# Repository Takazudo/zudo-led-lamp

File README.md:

# zudo-led-lamp

USB-PD powered LED lamp with fire/wave-like brightness modulation.

Docs: https://zudo-led-lamp.takazudomodular.com/

## Current build path

The current path is zudo-pd **P15 r1** (27 × 40 mm, 3 A NVM image) with the two existing
Board Ls, decided 2026-11-03. The two Board Ls already exist; the P15 modules are not ordered, programmed or measured. See the
[current path](candidates/README.md#current-path-p15-r1--the-two-existing-board-ls) for the
exact revisions and hashes, and the
[before-programming checklist](firmware/board-l/BEFORE-PROGRAMMING-CHECKLIST.md) before any
power-on. `boards/board-p/` remains the as-ordered 2026-09-19 Board P reference.
The [current state and completion page](doc/src/content/docs/architecture/current-state.mdx)
lists what is ordered, programmed and measured, and the owner actions in order.

Start the two-P15 order preparation at the [prototype-order handoff](manufacturing/README.md).
Supplier preview, order-day availability and total cost remain owner checkout gates.

## Repo layout

- `doc/` — zudo-doc documentation site (source of truth for specs, notes, and build logs)
- `boards/board-p/` — KiCad project: USB-PD front end board
- `boards/board-l/` — KiCad project: driver + control + LED array board
- `boards/swd-adapter/` — KiCad project: ST-LINK/V2 20-pin to Board L 1x5 SWD adapter
- `enclosure/` — parametric starburst enclosure generator and [print/assembly guide](enclosure/README.md)
- `symbols/`, `footprints/` — shared KiCad symbol/footprint/3D libraries for all projects (see `footprints/CLAUDE.md`)

## Component selection

Read the [draft selection and socket comparison guidance](doc/src/content/docs/architecture/component-selection-guidelines.mdx) before proposing parts. Exact evidence ownership remains in the component-spec-audit inventory.

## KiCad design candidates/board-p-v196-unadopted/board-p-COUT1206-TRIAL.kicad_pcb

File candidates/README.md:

# Isolated hardware candidates — NOT ADOPTED

Directories here hold isolated design candidates imported from outside Git history
for review. They are not canonical hardware: `boards/` and
`manufacturing/` remain the source of truth for what was ordered. Nothing here is
validated, qualified, released, or order-ready, and no fabrication output may be
generated from it without a separate explicit approval.

## Current path: P15 r1 + the two existing Board Ls

**Decision 2026-11-03 (owner):** the LED lamp's current Board P is the zudo-pd
**P15 r1**, shared with the 15 V zudo-pd product, mated with the **two existing Board Ls**
from the 2026-09-19 order. LED-first. The Board Ls already exist; P15 is not ordered, programmed or
measured yet.

| Item | Current value | Where it lives |
| --- | --- | --- |
| Board P | zudo-pd `boards/board-p15/` r1, 27 × 40 mm, same outline, holes and JOUT1 as the ordered LED Board P | Adopted at zudo-pd commit `4a0741fabf8d2332848a3740708aab26b8504133` (now on zudo-pd `main`). Consumer reference: [`boards/p15-r1-reference.json`](../boards/p15-r1-reference.json), checked by `python3 scripts/checks/verify-p15-reference.py --pd-repo <zudo-pd checkout>` (byte identity only) |
| NVM image | `boards/board-p15/nvm/stusb4500-15v.bin`: 2 PDOs, PDO1 5 V / 1.5 A, PDO2 15 V / **3 A**, POWER_ONLY_ABOVE_5V = 1. Same image for LED and zudo-pd | SHA256 `76622e14862e53cf318b24eb662f7dc9f34d48134867cf954b30c195c26e8eeb` at that commit. Desk image: never written or read back |
| Board L | The two existing boards, unchanged: RS1 = 200 mΩ as built, MCU believed blank | `boards/board-l/`, `manufacturing/jlcpcb/2026-09-19/` |
| Firmware | `firmware/board-l/target/` with `CTRL_FULL_CCR` = 2407 (the 200 mΩ ceiling) | Not flashed. See [`firmware/board-l/BEFORE-PROGRAMMING-CHECKLIST.md`](../firmware/board-l/BEFORE-PROGRAMMING-CHECKLIST.md) |
| Bench sheets | Boot, NTC, knob, CTRL, option bytes, temperature | [`firmware/board-l/BENCH-TEST-SHEETS.md`](../firmware/board-l/BENCH-TEST-SHEETS.md), all NOT EXECUTED |

Accepted residuals and mandatory steps (they are not passes):

- P15 has no NVM-independent voltage window or eFuse. Requirement rows R2.3, R2.4 and
  R2.6 are **FAIL** and R2.5 is **UNKNOWN**; the owner accepted this as a prototype-stage
  residual. The adoption does not turn them into passes.
- Every P15 unit must have its NVM written and accepted (P15-NVM-4/5 on a 5 V-only source,
  then P15-NVM-6 on a PD test source with no load) before it ever mates with a Board L.
  The procedure is owned by zudo-pd (`doc/src/content/docs/architecture/board-p15-programming.md`).
- Keep `CTRL_FULL_CCR` = 2407 while RS1 = 200 mΩ. The [#52 analysis](board-l-led-margin-52/ANALYSIS.md)
  hot-branch numbers (88.6 / 96.9 mA at full CTRL) and the 250 mΩ rework numbers
  (72.5 / 79.1 mA) are sensitivity cases, not measured values or guaranteed limits. Do not
  rework RS1 or move to 3200 as an assumed next step.

Enclosure fit in CAD (2026-11-03, P15P): `enclosure/generate.py` at `cfc8cb4`, run in an isolated
copy with `boards/board-p/board-p.kicad_pcb` replaced by the zudo-pd P15 r1 PCB (sha256 `97acc5f4…`)
and its 3D models, KiCad 10.0.6 pinned image, exit 0. All generator assertions and `check_stack` pass,
every printed part clears every P15 and Board L STEP body (0.0 mm³), and the USB corridor is open.
Tracked enclosure outputs were not regenerated. Nominal datums only; print and seating fit are unmeasured.
Use the [LED prototype-order handoff](../manufacturing/README.md) for the pinned owner decision packet,
exact three upload files, supporting exclusions and remaining checkout checks. For LED, 2 P15 are new,
the 2 Board Ls are reused, and no new Board B is ordered.

These are **not** blockers for the current path: the PDO2 1.5 A vs 3 A question (settled:
3 A), the 27 × 44 / 27 × 50 outline question, and the old Board P #144 diagnosis. They
belong to the future candidates below.

## Future candidates (not on the current path)

| Directory | Candidate | State |
| --- | --- | --- |
| [`board-p-v196-unadopted/`](board-p-v196-unadopted/PROVENANCE.md) | HUSB238_006DD 15 V-only shared Board P, V196 routed PCB | FUTURE CANDIDATE. UNADOPTED; native DRC exit 5 (22 known findings), not DRC PASS |
| [`board-p-v198-unadopted/`](board-p-v198-unadopted/PROVENANCE.md) | V196 + PCB/schematic field sync, J1 bound to USB4105-GF-A / C3020560 | FUTURE CANDIDATE. UNADOPTED; same 22 DRC findings (exit 5), not DRC PASS |
| [`board-p-v199-pending-user-decision/`](board-p-v199-pending-user-decision/PROVENANCE.md) | V198 + recommended options as separable changes: RMH2 187k, COUT Datasheet sync, J1 GND 0.025 mm trim, SMAJ20A input TVS | FUTURE CANDIDATE (its options are no longer pending for the current path). UNADOPTED scratch; same 22 DRC findings with default rules (exit 5); 0 with the unapplied base rules in a scratch copy only |
| [`board-p-rnext-stusb-unadopted/`](board-p-rnext-stusb-unadopted/README.md) | LED Board P r-next schematic: zudo-pd common STUSB4500 block @3ac13d46 + LED voltage window after Q1 + JOUT1; option pair PDO2 1.5 A / RILM 3.32 k or 3 A / 1.27 k (candidate-only question) | **FUTURE CANDIDATE** (deferred 2026-11-03; its PDO2 and outline options are not current blockers). UNADOPTED schematic draft; native netlist matches spec, ERC 0 errors / 13 pin-type warnings; 9 candidate owner bundles; land check; 27 × 40 mm placement study (no routing); area options (C3 / J3 / back side / outline) compared, J3 test-pad array adopted in candidate; no PCB |
| [`board-p-stusb-window-subcircuit/`](board-p-stusb-window-subcircuit/README.md) | LED Board P r-next voltage window (TPS3701 + TPS25947 + QINH driven by STUSB4500 VBUS_EN_SNK, RMH2 187 k, SMAJ20A input TVS) as a standalone sub-circuit | FUTURE CANDIDATE. UNADOPTED desk source; structural check + V196 arithmetic only; awaits the common STUSB4500 block |
| [`board-p-stusb4500-144-root-cause/`](board-p-stusb4500-144-root-cause/ANALYSIS.md) | Issue #144 desk root-cause ranking for the ordered STUSB4500 Board P and rules for the common controller block | Desk analysis only; nothing measured or changed. Not a prerequisite for the current path |
| [`board-l-led-margin-52/`](board-l-led-margin-52/ANALYSIS.md) | Issue #52 LED peak-current desk analysis: RS1 options vs firmware CTRL ceiling | UNADOPTED proposal; recommends RS1 = 250 mΩ (RLP25FEER250, LCSC unverified); no hardware changed. The current path keeps 200 mΩ with `CTRL_FULL_CCR` 2407 |
| [`FIRMWARE-V72-INVENTORY.md`](FIRMWARE-V72-INVENTORY.md) | Board L V72 portable C firmware, imported to [`firmware/board-l/`](../firmware/board-l/README.md) | Imported; the target skeleton in `firmware/board-l/target/` links it. Not flashed |

The KiCad project directories sit two levels below the repository root on purpose:
their library footprints resolve 3D models via
`${KIPRJMOD}/../../footprints/kicad/zudo-led-lamp.3dshapes/`.

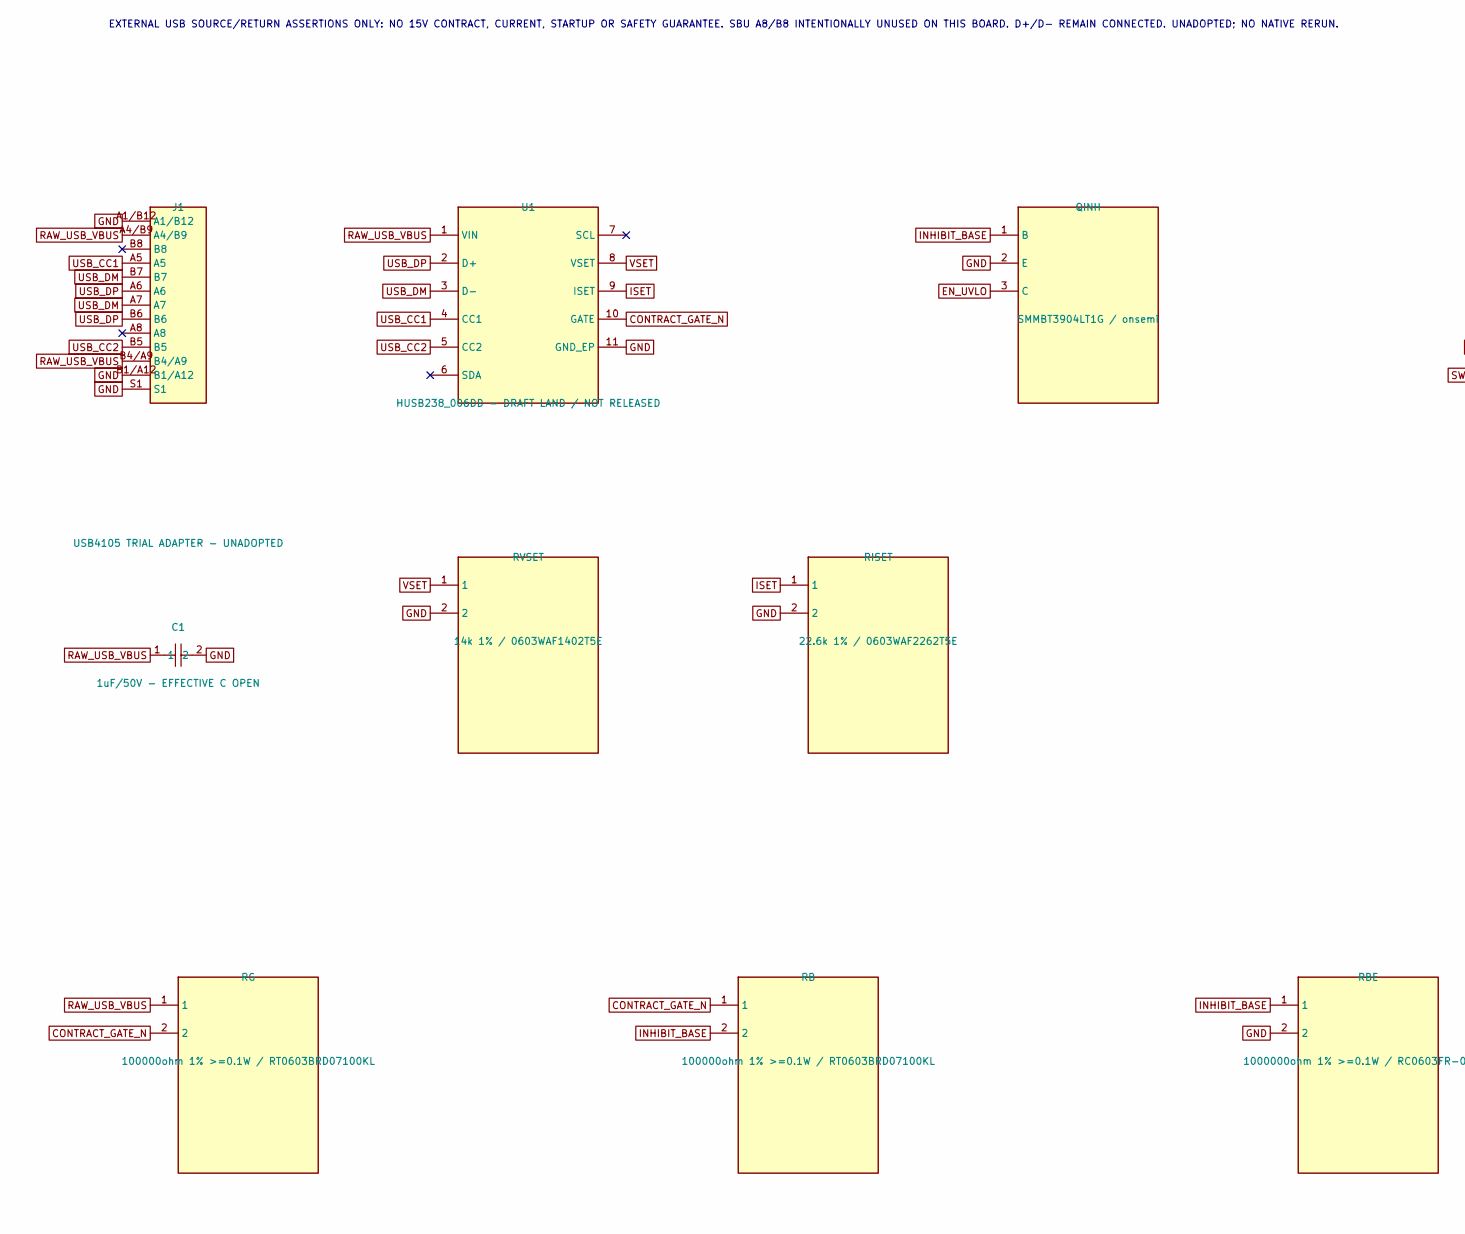
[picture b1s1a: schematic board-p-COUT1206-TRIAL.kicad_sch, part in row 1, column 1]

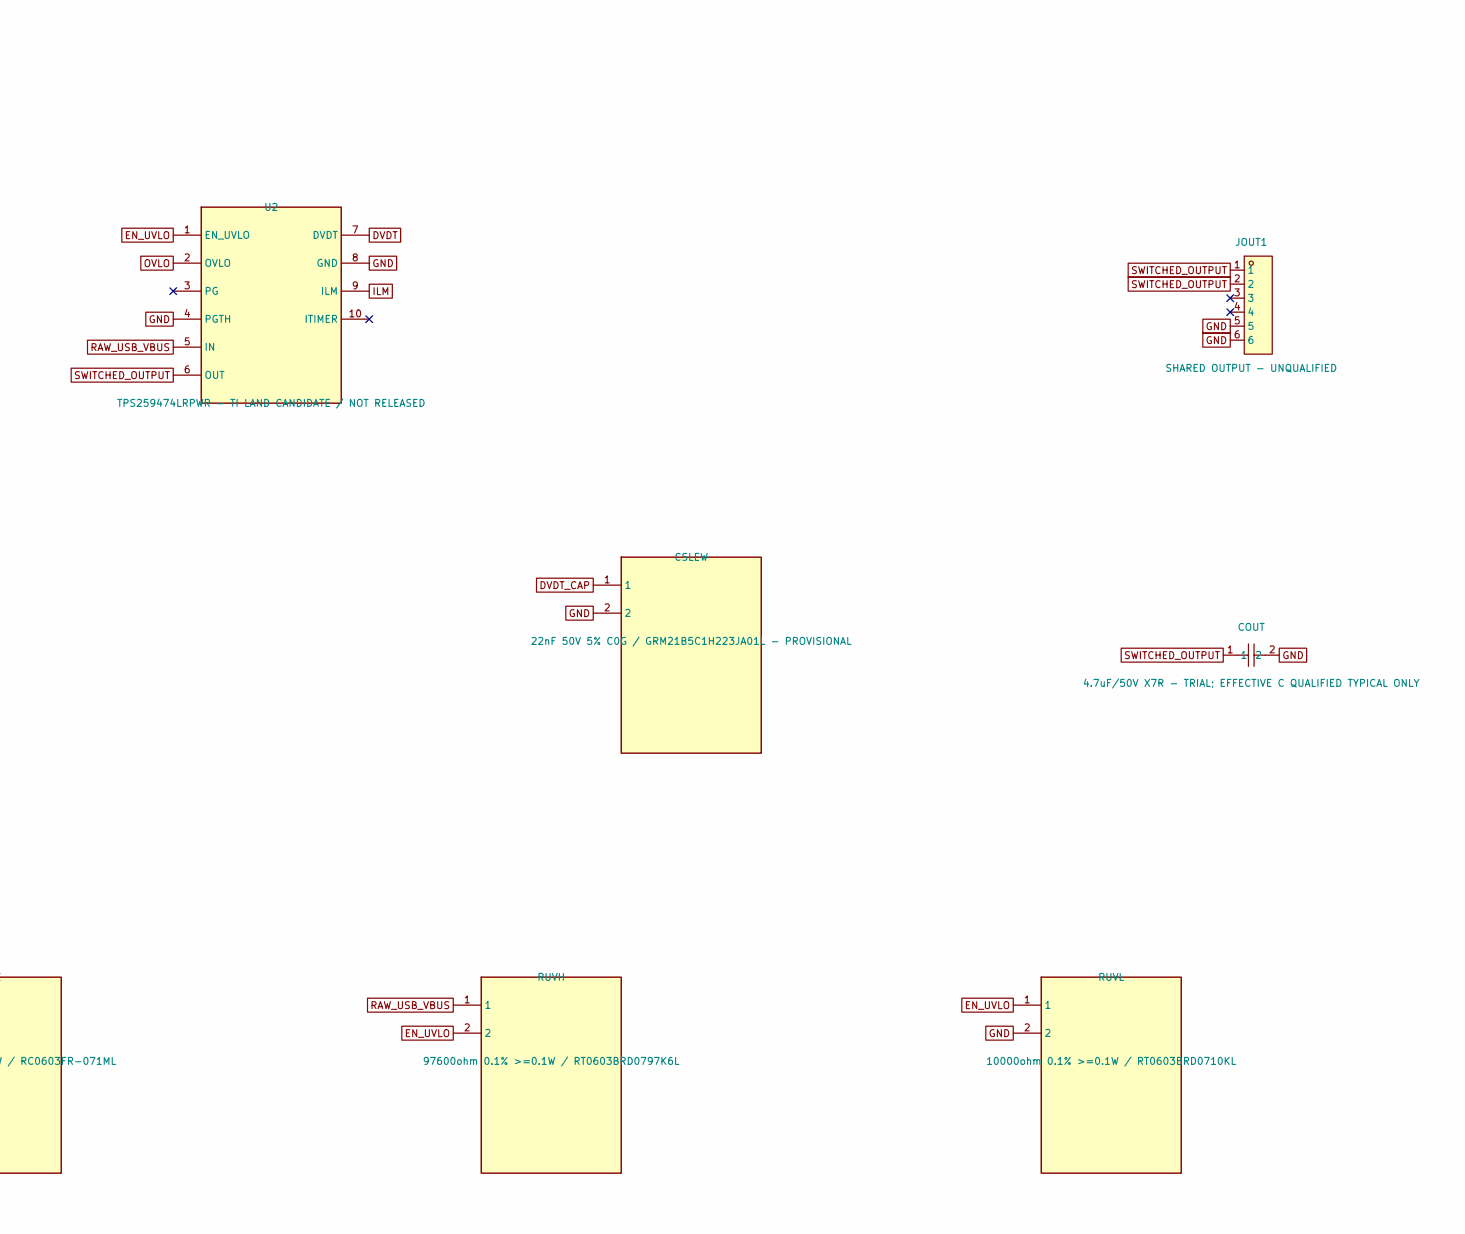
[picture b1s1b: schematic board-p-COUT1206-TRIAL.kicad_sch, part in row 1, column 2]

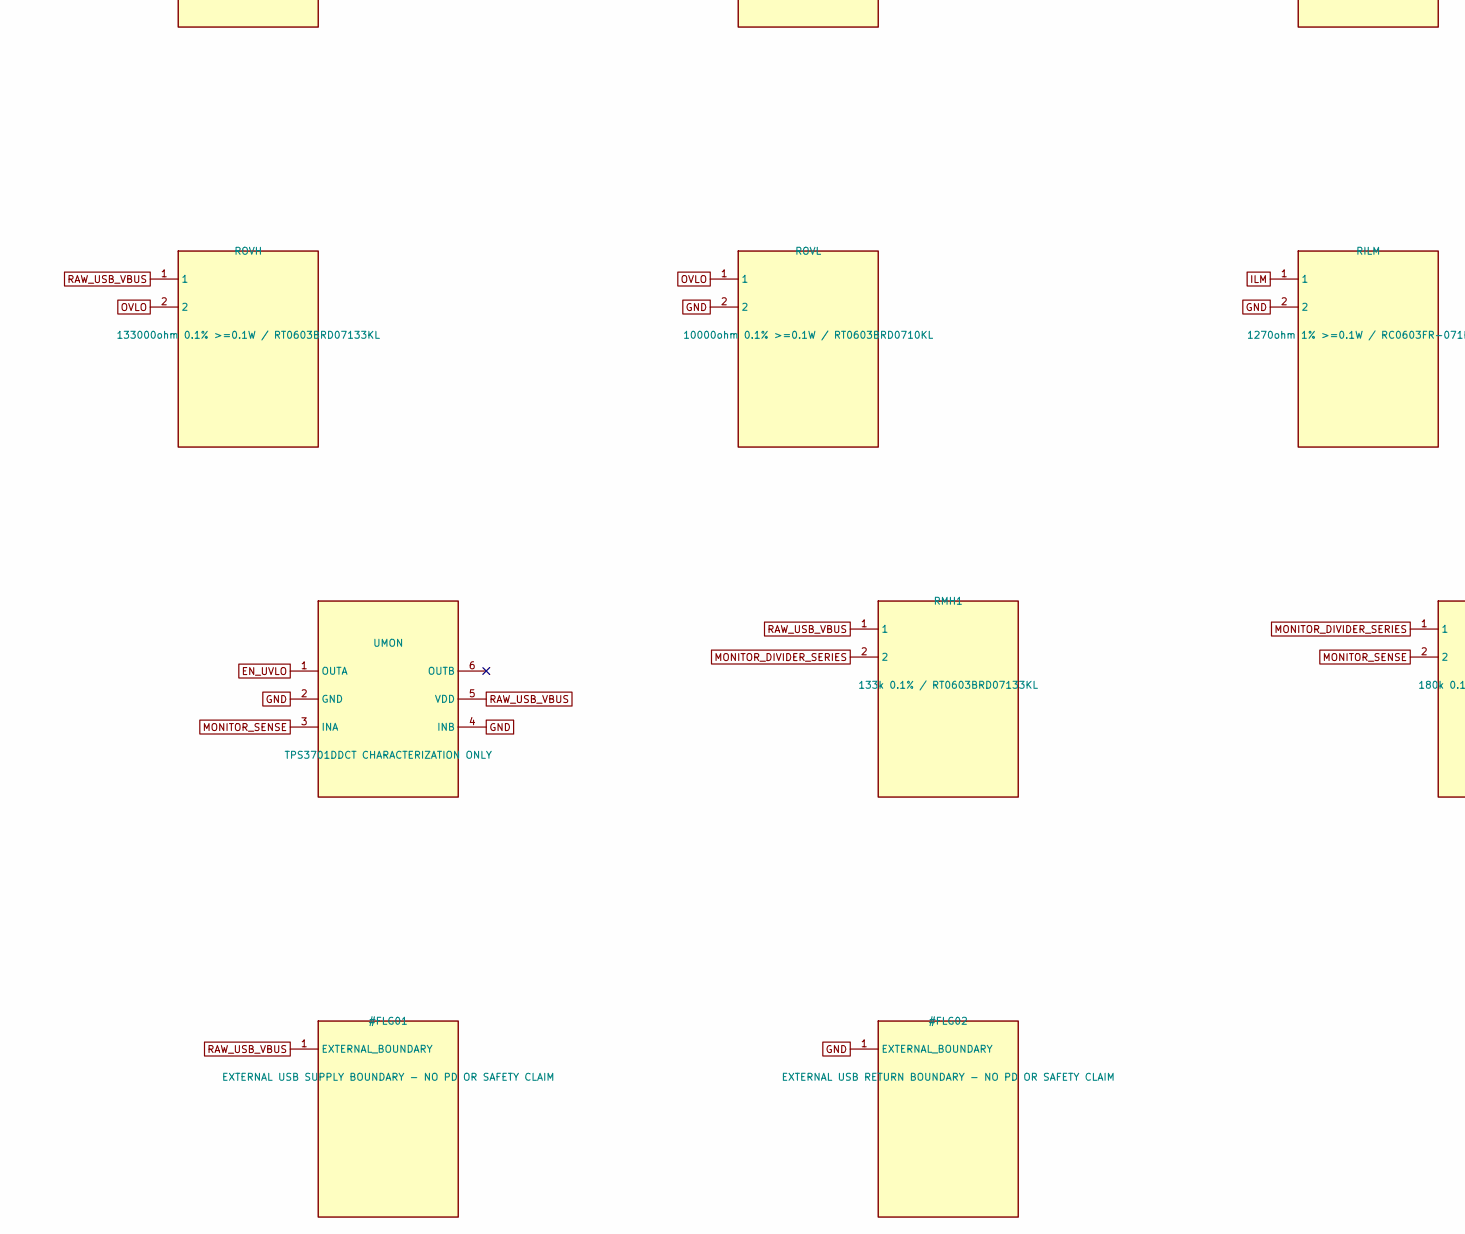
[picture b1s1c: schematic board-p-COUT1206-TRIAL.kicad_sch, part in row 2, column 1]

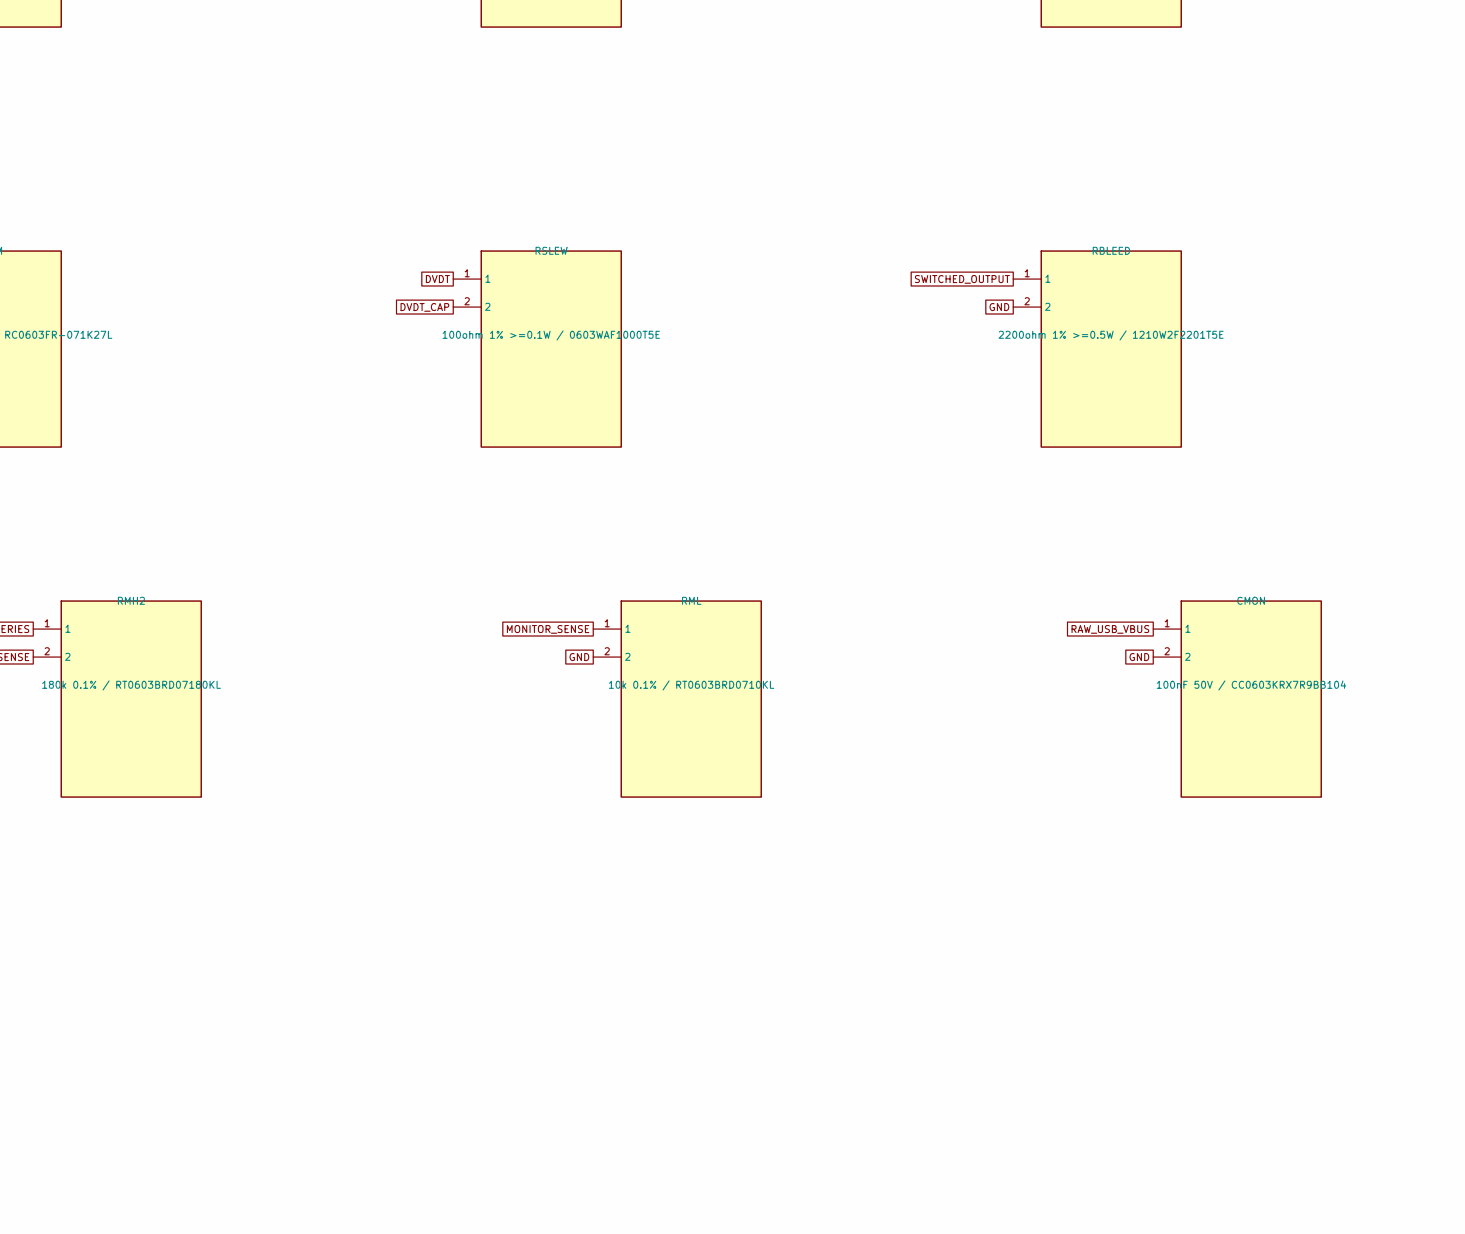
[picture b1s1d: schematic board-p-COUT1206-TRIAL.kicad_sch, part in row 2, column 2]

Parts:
C1: 1uF/50V - EFFECTIVE C OPEN; C0603; LCSC C15849
CMON: 100nF 50V / CC0603KRX7R9BB104; C0603; LCSC C14663
COUT: 4.7uF/50V X7R - TRIAL; EFFECTIVE C QUALIFIED TYPI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; COUT_CL31B475KBHNNNE_1206_TRIAL; MPN CL31B475KBHNNNE; LCSC C51205
CSLEW: 22nF 50V 5% C0G / GRM21B5C1H223JA01L - PROVISIONAL; GRM21B5C1H223JA01L_MURATA_REFLOW; LCSC C77069
J1: USB4105 TRIAL ADAPTER - UNADOPTED; USB4105_V106_TRIAL_UNASSIGNED
JOUT1: SHARED OUTPUT - UNQUALIFIED; HDR-TH_6P-P2.54-V-M; LCSC C492405
QINH: SMMBT3904LT1G / onsemi; SMMBT3904LT1G_CASE318_ONSEMI_EXAMPLE; LCSC C84555
RB: 100000ohm 1% >=0.1W / RT0603BRD07100KL; R0603; LCSC C122538
RBE: 1000000ohm 1% >=0.1W / RC0603FR-071ML; R0603; LCSC C105578
RBLEED: 2200ohm 1% >=0.5W / 1210W2F2201T5E; RBLEED_1210W2F2201T5E; LCSC C422361
RG: 100000ohm 1% >=0.1W / RT0603BRD07100KL; R0603; LCSC C122538
RILM: 1270ohm 1% >=0.1W / RC0603FR-071K27L; R0603; LCSC C245930
RISET: 22.6k 1% / 0603WAF2262T5E; R0603; LCSC C22959
RMH1: 133k 0.1% / RT0603BRD07133KL; R0603; LCSC C861111
RMH2: 180k 0.1% / RT0603BRD07180KL; RMH2_RT0603BRD07180KL_YAGEO_REFLOW_CANDIDATE; LCSC C326731
RML: 10k 0.1% / RT0603BRD0710KL; R0603; LCSC C95204
ROVH: 133000ohm 0.1% >=0.1W / RT0603BRD07133KL; R0603; LCSC C861111
ROVL: 10000ohm 0.1% >=0.1W / RT0603BRD0710KL; R0603; LCSC C95204
RSLEW: 100ohm 1% >=0.1W / 0603WAF1000T5E; R0603; LCSC C22775
RUVH: 97600ohm 0.1% >=0.1W / RT0603BRD0797K6L; R0603; LCSC C861608
RUVL: 10000ohm 0.1% >=0.1W / RT0603BRD0710KL; R0603; LCSC C95204
RVSET: 14k 1% / 0603WAF1402T5E; R0603; LCSC C22803
U1: HUSB238_006DD - DRAFT LAND / NOT RELEASED; HUSB238_DFN10_3x3_EP1.7x2.4_PASTE_PROPOSAL; LCSC C55013903
U2: TPS259474LRPWR - TI LAND CANDIDATE / NOT RELEASED; TPS259474_RPW0010A_TI_EXAMPLE; LCSC C2864845
UMON: TPS3701DDCT CHARACTERIZATION ONLY; TPS3701_DDC0006A_DRAFT; LCSC C132027

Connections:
CONTRACT_GATE_N: RB.1, RG.2, U1.10 (GATE)
DVDT: RSLEW.1, U2.7 (DVDT)
DVDT_CAP: CSLEW.1, RSLEW.2
EN_UVLO: QINH.3 (C), RUVH.2, RUVL.1, U2.1 (EN_UVLO), UMON.1 (OUTA)
GND: C1.2, CMON.2, COUT.2, CSLEW.2, J1.A1/B12, J1.B1/A12, J1.S1, JOUT1.5, JOUT1.6, QINH.2 (E), RBE.2, RBLEED.2, RILM.2, RISET.2, RML.2, ROVL.2, RUVL.2, RVSET.2, U1.11 (GND_EP), U2.4 (PGTH), U2.8 (GND), UMON.2 (GND), UMON.4 (INB)
ILM: RILM.1, U2.9 (ILM)
INHIBIT_BASE: QINH.1 (B), RB.2, RBE.1
ISET: RISET.1, U1.9 (ISET)
MONITOR_DIVIDER_SERIES: RMH1.2, RMH2.1
MONITOR_SENSE: RMH2.2, RML.1, UMON.3 (INA)
OVLO: ROVH.2, ROVL.1, U2.2 (OVLO)
RAW_USB_VBUS: C1.1, CMON.1, J1.A4/B9, J1.B4/A9, RG.1, RMH1.1, ROVH.1, RUVH.1, U1.1 (VIN), U2.5 (IN), UMON.5 (VDD)
SWITCHED_OUTPUT: COUT.1, JOUT1.1, JOUT1.2, RBLEED.1, U2.6 (OUT)
USB_CC1: J1.A5, U1.4 (CC1)
USB_CC2: J1.B5, U1.5 (CC2)
USB_DM: J1.A7, J1.B7, U1.3 (D-)
USB_DP: J1.A6, J1.B6, U1.2 (D+)
VSET: RVSET.1, U1.8 (VSET)

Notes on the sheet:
EXTERNAL USB SOURCE/RETURN ASSERTIONS ONLY: NO 15V CONTRACT, CURRENT, STARTUP OR SAFETY GUARANTEE. SBU A8/B8 INTENTIONALLY UNUSED ON THIS BOARD. D+/D- REMAIN CONNECTED. UNADOPTED; NO NATIVE RERUN.

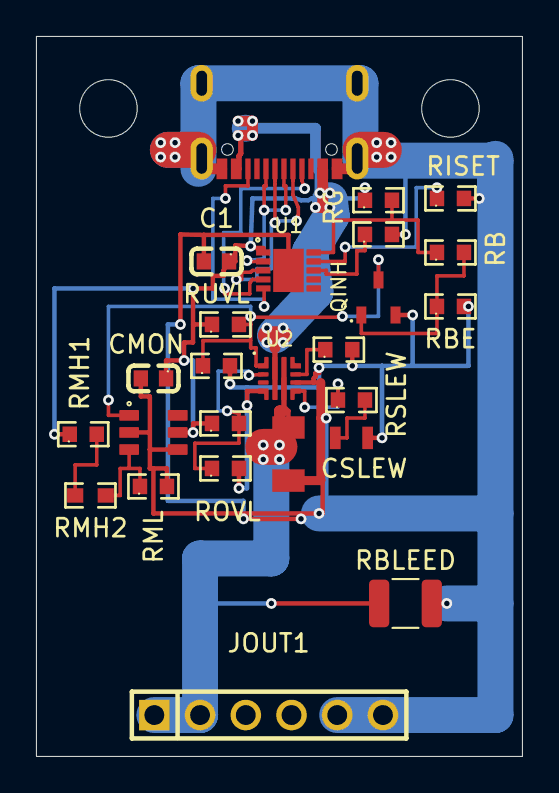
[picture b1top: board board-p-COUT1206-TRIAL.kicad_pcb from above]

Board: 2 copper layers, 27.0 x 40.0 mm, 27 parts (0 on the bottom side), 18 nets.

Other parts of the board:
MH1, MH2: 3.2mm NPTH - HARDWARE UNSELECTED; NPTH_3.2_SOURCE_TRIAL

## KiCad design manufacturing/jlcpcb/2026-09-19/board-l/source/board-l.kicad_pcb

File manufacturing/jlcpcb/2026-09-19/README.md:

# JLCPCB upload sets

Prepared for quoting and placement review; read ORDER-NOTES.md before checkout.

| Board | Gerber ZIP | BOM | CPL | Fitted parts |
| --- | --- | --- | --- | --- |
| board-p | [board-p-gerbers.zip](board-p/board-p-gerbers.zip) | [bom.csv](board-p/bom.csv) | [cpl.csv](board-p/cpl.csv) | 19 |
| board-l | [board-l-gerbers.zip](board-l/board-l-gerbers.zip) | [bom.csv](board-l/bom.csv) | [cpl.csv](board-l/cpl.csv) | 67 |
| swd-adapter | [swd-adapter-gerbers.zip](swd-adapter/swd-adapter-gerbers.zip) | [bom.csv](swd-adapter/bom.csv) | [cpl.csv](swd-adapter/cpl.csv) | 2 |

All intended fitted components, including all connector headers, are requested
for JLCPCB soldering. Intentional Board P DNP options remain excluded.

RV1 CPL rotation is corrected from 0 to 180 degrees, matching the user-adjusted
JLCPCB bottom preview on 2026-09-19. Do not apply that correction a second time.

Board L RV1: confirm manufacturer-compatible soldering and 1.6 mm board seating
with JLCPCB. Stock and their placement preview still need checkout review.

Checks: no DRC/ERC errors; no unrouted connections; BOM/CPL identities and
population match; Gerber/drill ZIPs independently parsed and rendered.
Existing DRC/ERC warnings are retained under each board/checks directory.

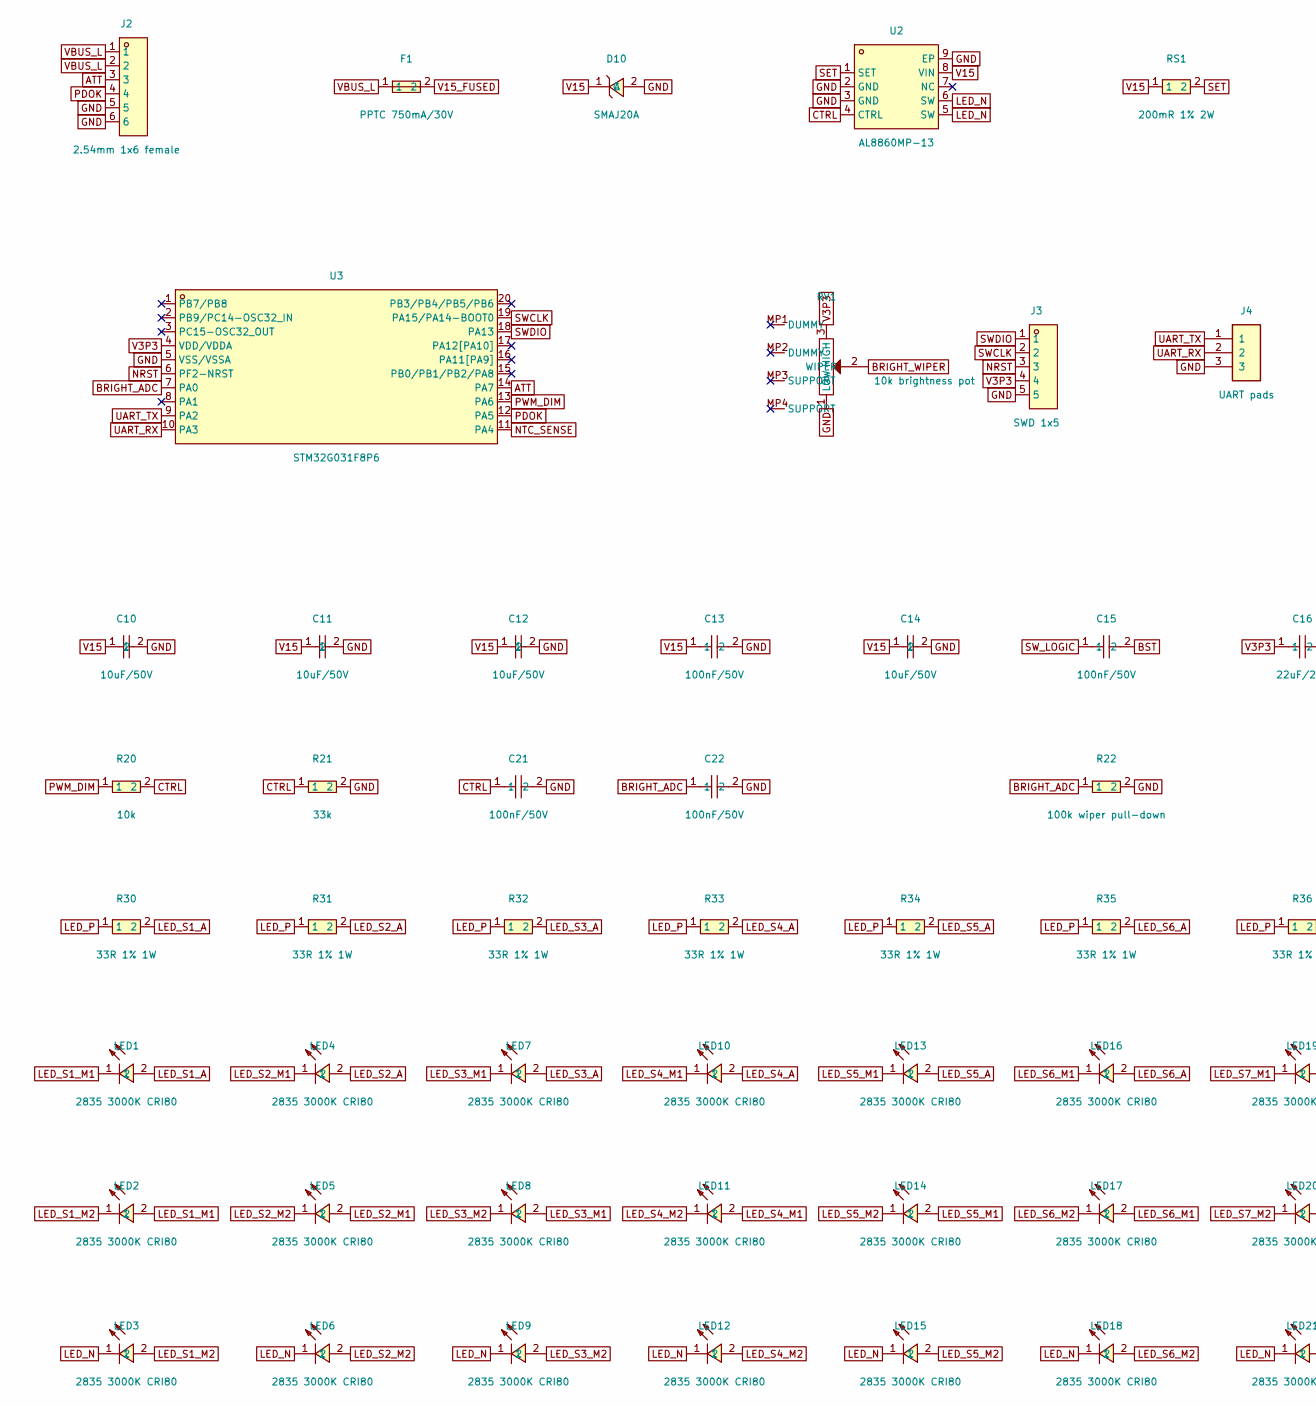
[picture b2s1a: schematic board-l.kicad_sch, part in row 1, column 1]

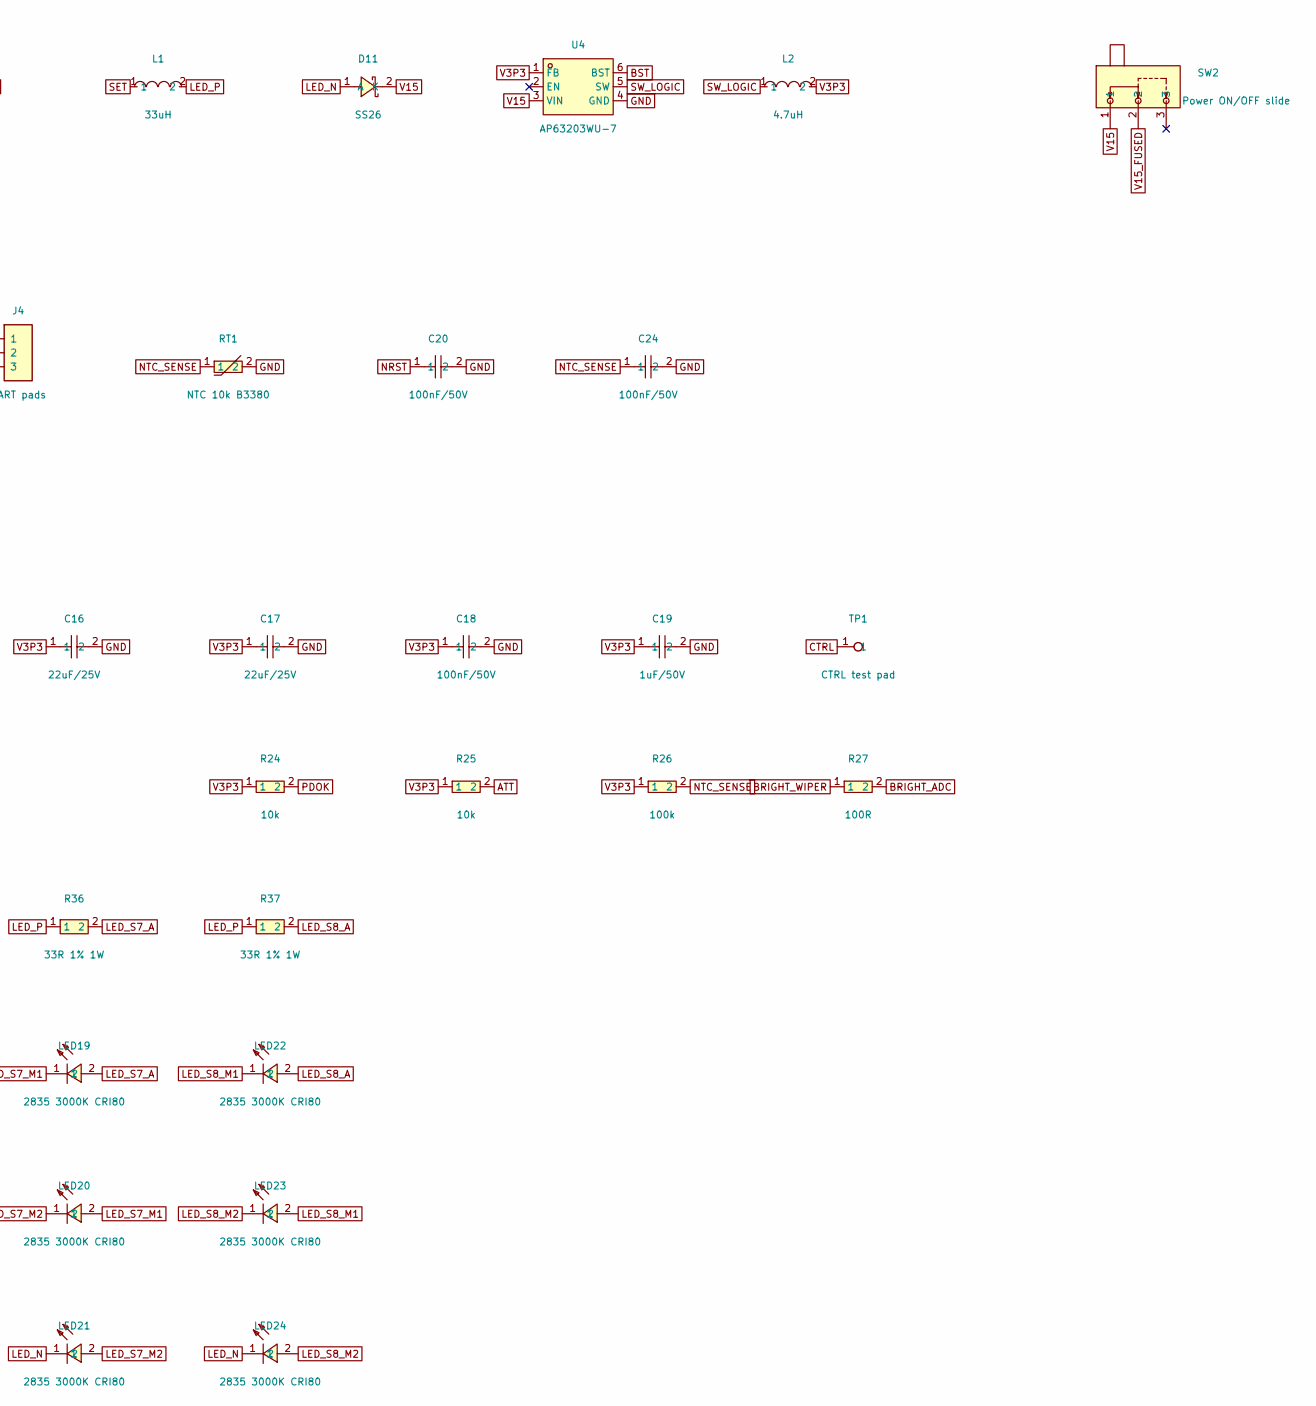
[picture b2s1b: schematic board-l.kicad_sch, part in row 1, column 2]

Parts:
C10, C11, C12, C14: 10uF/50V; C1206; LCSC C13585
C13, C15, C18, C20, C21, C22, C24: 100nF/50V; C0603; LCSC C14663
C16, C17: 22uF/25V; C0805; LCSC C45783
C19: 1uF/50V; C0603; LCSC C15849
D10: SMAJ20A; SMA_L4.2-W2.6-LS5.3-RD; LCSC C571370
D11: SS26; SMA_L4.3-W2.6-LS5.0-FD; LCSC C7420363
F1: PPTC 750mA/30V; F1206; LCSC C976305
J2: 2.54mm 1x6 female; HDR-TH_6P-P2.54-V-F; LCSC C2832269
J3: SWD 1x5; HDR-TH_5P-P2.54-V-M; LCSC C492404
J4: UART pads; PogoPad_1x03_P2.54mm
L1: 33uH; IND-SMD_L7.0-W6.6_FXL0630; LCSC C177245
L2: 4.7uH; IND-SMD_L4.0-W4.0_FNR40XXS; LCSC C167874
LED1, LED2, LED3, LED4, LED5, LED6, LED7, LED8, LED9, LED10, LED11, LED12, LED13, LED14, LED15, LED16, LED17, LED18, LED19, LED20, LED21, LED22, LED23, LED24: 2835 3000K CRI80; LED-SMD_L3.3-W2.8-RD; LCSC C210315
R20, R24, R25: 10k; R0805; LCSC C17414
R21: 33k; R0603; LCSC C4216
R22: 100k wiper pull-down; R0603; LCSC C25803
R26: 100k; R0603; LCSC C25803
R27: 100R; R0603; LCSC C22775
R30, R31, R32, R33, R34, R35, R36, R37: 33R 1% 1W; R2512; LCSC C2934070
RS1: 200mR 1% 2W; R2512; LCSC C459674
RT1: NTC 10k B3380; R0603; LCSC C13564
RV1: 10k brightness pot; POT-TH_RK10J11E0034; LCSC C470643
SW2: Power ON/OFF slide; SW-TH_SS-12D01-G020; LCSC C5446803
TP1: CTRL test pad; TestPad_D1.5mm
U2: AL8860MP-13; MSOP-8_L3.0-W3.0-P0.65-LS4.9-BL-EP1.8; LCSC C500782
U3: STM32G031F8P6; TSSOP-20_L6.5-W4.4-P0.65-LS6.4-BL; LCSC C529334
U4: AP63203WU-7; TSOT-26_L2.9-W1.6-P0.95-LS2.8-BL; LCSC C780769

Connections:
ATT: J2.3, R25.2, U3.14 (PA7)
BRIGHT_ADC: C22.1, R22.1, R27.2, U3.7 (PA0)
BRIGHT_WIPER: R27.1, RV1.2 (WIPER)
BST: C15.2, U4.6 (BST)
CTRL: C21.1, R20.2, R21.1, TP1.1 (1_1), U2.4 (CTRL)
GND: C10.2, C11.2, C12.2, C13.2, C14.2, C16.2, C17.2, C18.2, C19.2, C20.2, C21.2, C22.2, C24.2, D10.2 (A), J2.5, J2.6, J3.5, J4.3, R21.2, R22.2, RT1.2, RV1.1 (LOW), U2.2 (GND), U2.3 (GND), U2.9 (EP), U3.5 (VSS/VSSA), U4.4 (GND)
LED_N: D11.1 (A), LED3.1, LED6.1, LED9.1, LED12.1, LED15.1, LED18.1, LED21.1, LED24.1, U2.5 (SW), U2.6 (SW)
LED_P: L1.2, R30.1, R31.1, R32.1, R33.1, R34.1, R35.1, R36.1, R37.1
LED_S1_A: LED1.2, R30.2
LED_S1_M1: LED1.1, LED2.2
LED_S1_M2: LED2.1, LED3.2
LED_S2_A: LED4.2, R31.2
LED_S2_M1: LED4.1, LED5.2
LED_S2_M2: LED5.1, LED6.2
LED_S3_A: LED7.2, R32.2
LED_S3_M1: LED7.1, LED8.2
LED_S3_M2: LED8.1, LED9.2
LED_S4_A: LED10.2, R33.2
LED_S4_M1: LED10.1, LED11.2
LED_S4_M2: LED11.1, LED12.2
LED_S5_A: LED13.2, R34.2
LED_S5_M1: LED13.1, LED14.2
LED_S5_M2: LED14.1, LED15.2
LED_S6_A: LED16.2, R35.2
LED_S6_M1: LED16.1, LED17.2
LED_S6_M2: LED17.1, LED18.2
LED_S7_A: LED19.2, R36.2
LED_S7_M1: LED19.1, LED20.2
LED_S7_M2: LED20.1, LED21.2
LED_S8_A: LED22.2, R37.2
LED_S8_M1: LED22.1, LED23.2
LED_S8_M2: LED23.1, LED24.2
NRST: C20.1, J3.3, U3.6 (PF2-NRST)
NTC_SENSE: C24.1, R26.2, RT1.1, U3.11 (PA4)
PDOK: J2.4, R24.2, U3.12 (PA5)
PWM_DIM: R20.1, U3.13 (PA6)
SET: L1.1, RS1.2, U2.1 (SET)
SWCLK: J3.2, U3.19 (PA15/PA14-BOOT0)
SWDIO: J3.1, U3.18 (PA13)
SW_LOGIC: C15.1, L2.1, U4.5 (SW)
UART_RX: J4.2, U3.10 (PA3)
UART_TX: J4.1, U3.9 (PA2)
V3P3: C16.1, C17.1, C18.1, C19.1, J3.4, L2.2, R24.1, R25.1, R26.1, RV1.3 (HIGH), U3.4 (VDD/VDDA), U4.1 (FB)
V15: C10.1, C11.1, C12.1, C13.1, C14.1, D10.1 (C), D11.2 (K), RS1.1, SW2.1, U2.8 (VIN), U4.3 (VIN)
V15_FUSED: F1.2, SW2.2
VBUS_L: F1.1, J2.1, J2.2

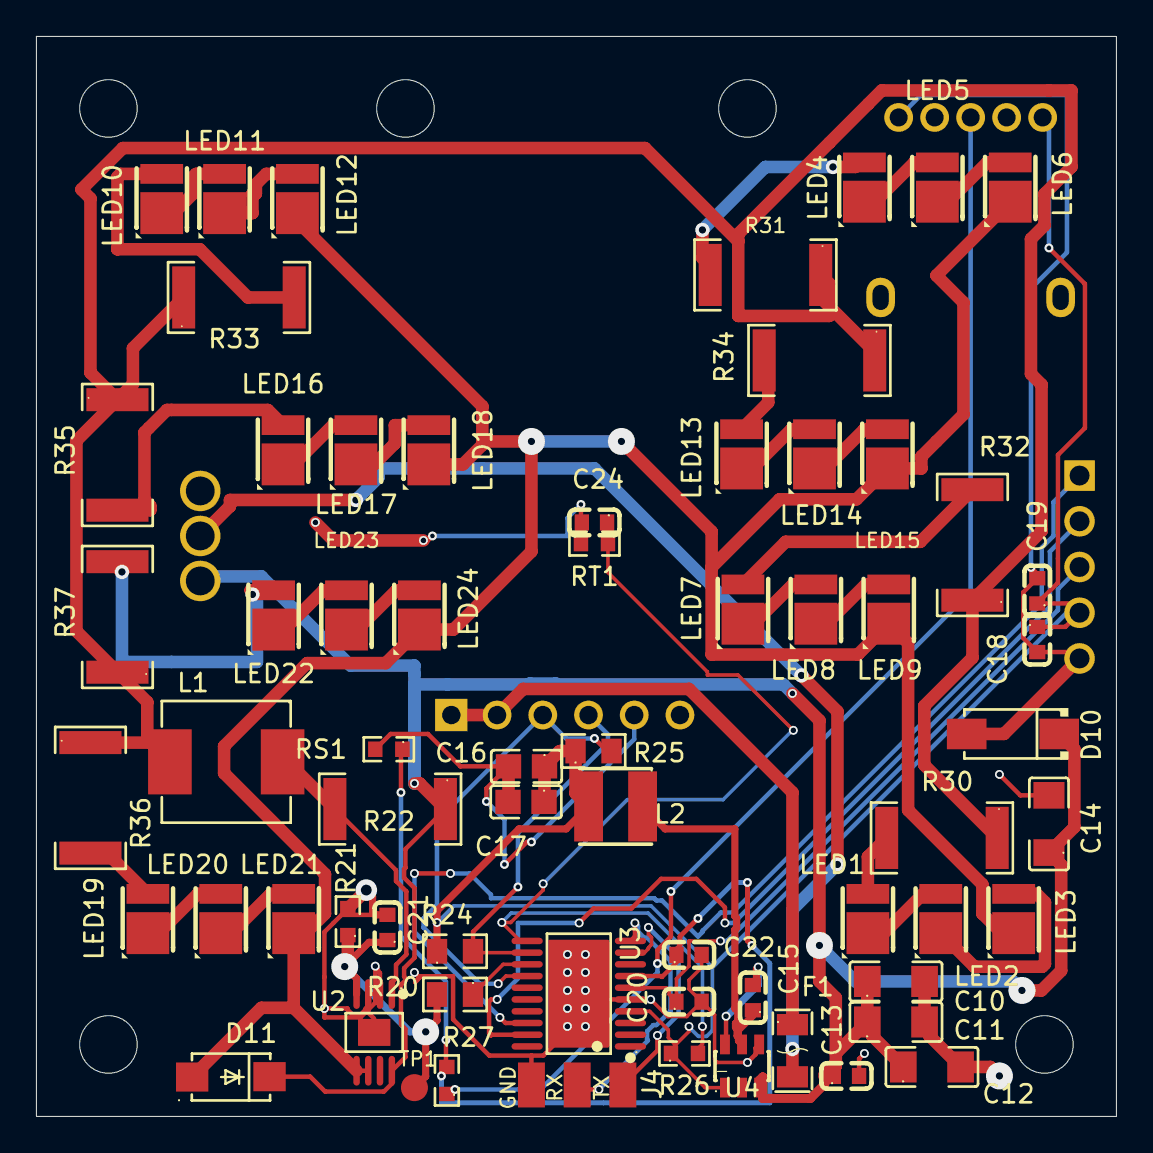
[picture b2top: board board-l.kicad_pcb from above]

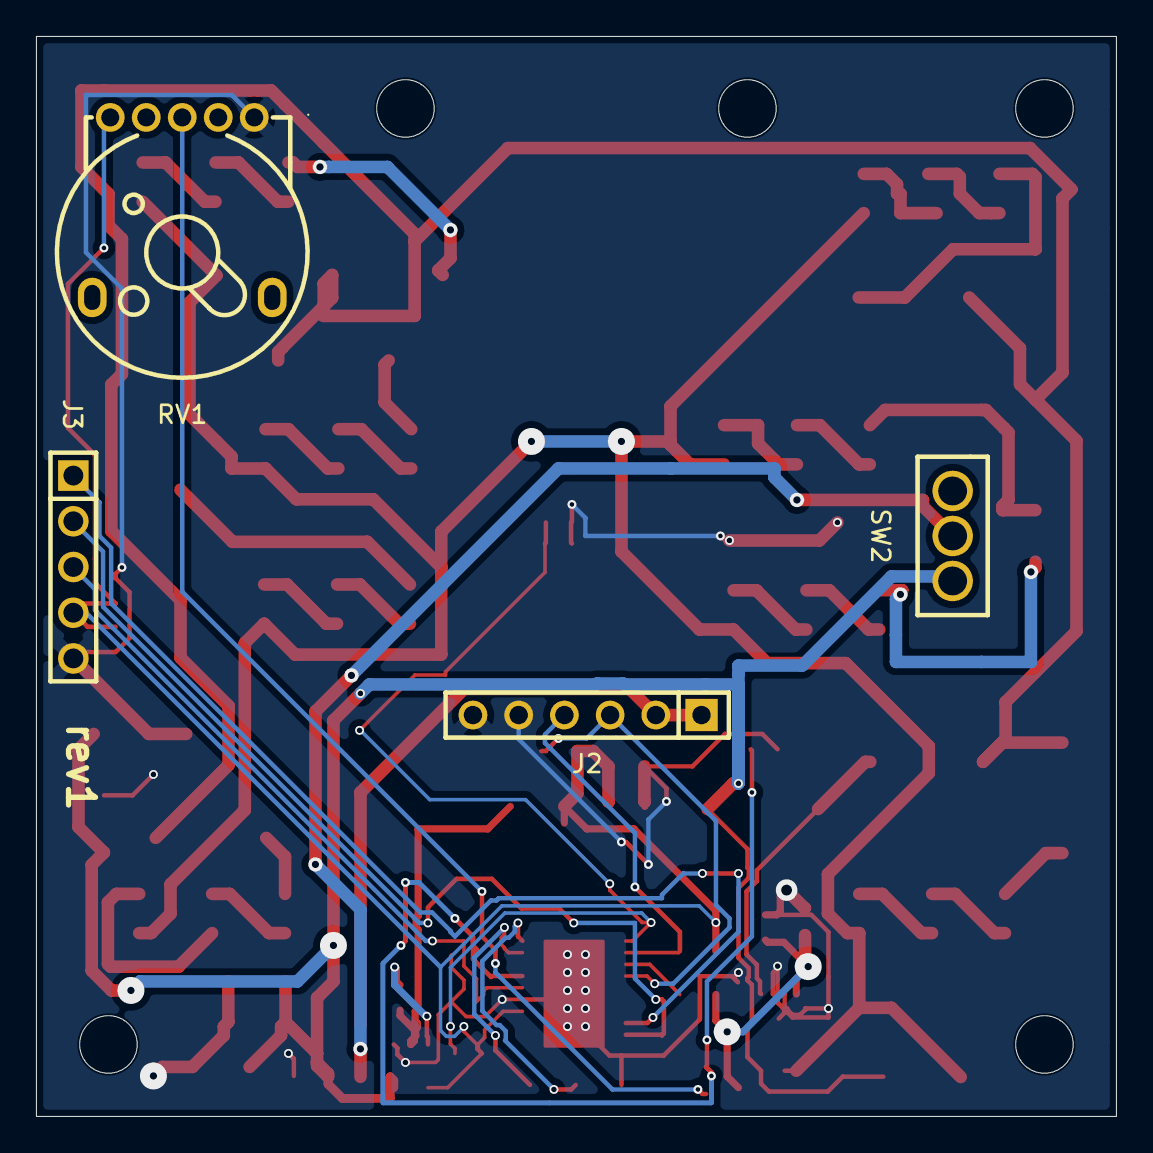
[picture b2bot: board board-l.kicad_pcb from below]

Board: 2 copper layers, 60.0 x 60.0 mm, 69 parts (4 on the bottom side), 46 nets.
